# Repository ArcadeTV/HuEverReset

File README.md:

## HuEverReset
InGame-Reset for PC Engine with support for TurboEverdrive v1-v2.5

_*Important!*_ - Please consider waiting until everything is confirmed working.

### v20221109 / ArcadeTV

---

#### Description:
This enables an InGame-Reset by pressing a button-combo on the controller that also works with TurboEverdrive to get back to the menu.
It is designed for the white japanese PC Engine console but can be easily adapted to any PC Engine system if you know which pins of the controller-input-socket to connect to the pcb. Optionally you can use a piezo speaker for acoustic feedback upon triggering a reset.

---

#### Parts

| Part | Value               | Device           | Package             |
| :--- | :------------------ | :--------------- | :------------------ |
| CB1  | 100nF               | C-USC0805        | C0805               |
| C1   | 220uF               | CPOL-USC/6032-28R| C/6032-28R          |
| D1   | RB168VWM-40TR       | RB168VWM-40TR    | RB168VWM40TR        |
| IC1  | ATTINY84V-10SSUR    | ATTINY84V-10SSUR | SOIC127P600X175-14N |
| IC2  | KA78R05CTU_NL       | KA78R05          | TO-220-4            |
| R1   | 20K                 | R-US_R0805       | R0805               |
| R2   | 10K                 | R-US_R0805       | R0805               |
| R3   | 220                 | R-US_R0805       | R0805               |
| HDR  | 3-Pin Header 2.54mm | Pinheader        | Pinheader 2.54mm    |

Optionally, a piezo speaker like the [KPM-1205A](https://datasheetspdf.com/pdf/868392/Ningbo/KPM-1205A/1). A 220 Ohms resistor is recommended on the positive leg for attenuation. You can also wire a switch to the pads of J1 if you want to toggle this feature on and off.

Also optional a 5V Common Cathode LED can be used for visual feedback. It's lit constantly until the button combo is pressed, then it flashes to indicate that a reset will occur if the combo is pressed longer and finally it goes off while the reset is performed.

Here's a [BOM file in Excel format](https://github.com/ArcadeTV/HuEverReset/raw/main/BOM_HuEverReset_Mouser.xlsx) that you can use to order parts at Mouser. It does not include the KA78R05 regulator, LED and piezo speaker. Also please note that due to a general chip shortage you may have to source the ATtiny84 somewhere else.

---

#### Installation:
See the [wiki](https://github.com/ArcadeTV/HuEverReset/wiki)

---

#### Technical:
Since a TurboEverdrive v1 to v2.5 is not listening to a hard reset (/RESET), implementing an IngameReset that is triggered upon pressing a button-combo on the controller is not possible. This mod solves that problem by replacing the 7805 regulator with a KA78R05 that has a switchable output. So, instead of pulling the /RESET line of the PC Engine LOW, this mod aims to cut the power of the system for 1 second and turning it back on. This ensures that the menu of the TurboEverdrive is displayed. The pcb consists of 2 different layouts including a little POWER BOARD for making the replacement of the power-regulator a breeze.

---

#### Microcontroller:
```
ATtiny84 ----------------
                          _____
            VCC  (  ) 01-|°    |-14 (  ) GND
Jmp: Use Speaker (10) 02-|     |-13 (00) ENABLE (MiniDin 7)
     Speaker (+) (09) 03-|     |-12 (01) D3: Run, Left (MiniDin 5)
            N.C. (11) 04-|     |-11 (02) D2: Select, Down (MiniDin 4)
             LED (08) 05-|     |-10 (03) D1: II, Right (MiniDin 3)
            N.C. (07) 06-|     |-09 (04) SELECT (MiniDin 6)
          /RESET (06) 07-|_____|-08 (05) D0: I, Up (MiniDin 2)

| Fuses: 
| -----------
| low:   0xE2
| high:  0xD7
| ext.:  0xFF
| lock:  0xFF
```
Please mind that the ATtiny84 microcontroller needs to be programmed
with the provided hex file. If you use the ISP header on the pcb, please do so while the board is unpopulated except for IC1.

---

#### Jumper J1
Enable or Disable the use of a piezo speaker (buzzer).
```
Closed: use
Open: ignore
```
If you connect a piezo speaker for acoustic feedback when a reset is triggered, close J1. You may want to use a resistor on the positive leg of the speaker (e.g. 220 Ohms) if you find it too loud.

---

#### PCB

Use the provided gerber files to order your pcb from your favorite manufacturer. 
I recommend jlcpcb. When ordering from jlcpcb, fill out the order-form as follows:

```
Different Design: 2
Delivery Format: Panel by Customer
PCB Thickness: 0.8 - 1.0 mm
```

**GERBER** files can be downloaded from the `releases` tab: 

https://github.com/ArcadeTV/HuEverReset/releases/latest

Eagle source files for editing also exist in this repository.

---

#### Thanks

NeoRame, Astrocade & micro

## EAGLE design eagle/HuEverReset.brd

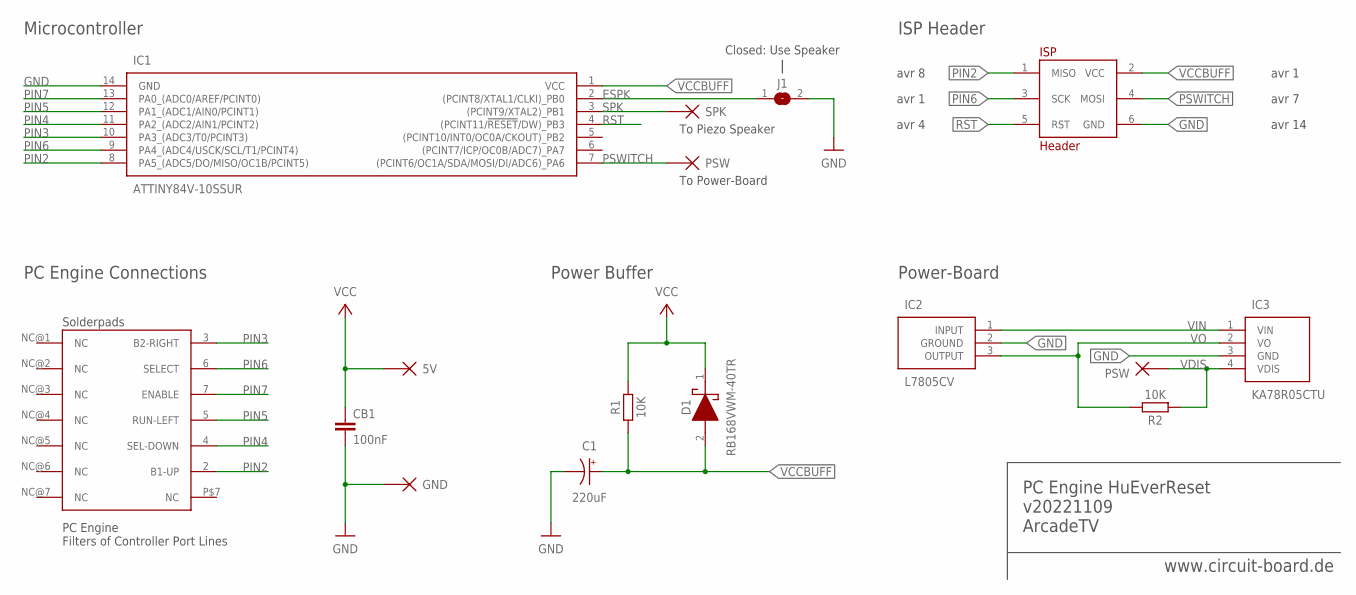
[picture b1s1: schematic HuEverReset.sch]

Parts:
C1: 220uF; C/6032-28R
CB1: 100nF; Z0805
D1: RB168VWM-40TR; RB168VWM40TR
IC1: ATTINY84V-10SSUR; SOIC127P600X175-14N
IC2: L7805CV; TO255P460X1020X2008-3P
IC3: KA78R05CTU; PADS
ISP: Header; TINY
J1: SJ
P1: 5V; PADS
P2: GND; PADS
P3: PSW; PADS
P4: SPK; PADS
R1, R2: 10K; Z0805
U$1: PCE-CNTRL-FILTERS
U$2: PSW; PADS

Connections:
ESPK: IC1.2 ((PCINT8/XTAL1/CLKI)_PB0), J1.1
GND: C1.-, CB1.2, IC1.14 (GND), IC2.2 (GROUND), IC3.3 (GND), ISP.6 (GND), J1.2, P2.P$1
PIN2: IC1.8 (PA5_(ADC5/DO/MISO/OC1B/PCINT5)), ISP.1 (MISO), U$1.2 (B1-UP)
PIN3: IC1.10 (PA3_(ADC3/T0/PCINT3)), U$1.3 (B2-RIGHT)
PIN4: IC1.11 (PA2_(ADC2/AIN1/PCINT2)), U$1.4 (SEL-DOWN)
PIN5: IC1.12 (PA1_(ADC1/AIN0/PCINT1)), U$1.5 (RUN-LEFT)
PIN6: IC1.9 (PA4_(ADC4/USCK/SCL/T1/PCINT4)), ISP.3 (SCK), U$1.6 (SELECT)
PIN7: IC1.13 (PA0_(ADC0/AREF/PCINT0)), U$1.7 (ENABLE)
PSWITCH: IC1.7 ((PCINT6/OC1A/SDA/MOSI/DI/ADC6)_PA6), ISP.4 (MOSI), P3.P$1
RST: IC1.4 ((PCINT11/!RESET!/DW)_PB3), ISP.5 (RST)
SPK: IC1.3 ((PCINT9/XTAL2)_PB1), P4.P$1
VCC: CB1.1, D1.1 (K), P1.P$1, R1.2
VCCBUFF: C1.+, D1.2 (A), IC1.1 (VCC), ISP.2 (VCC), R1.1
VDIS: IC3.4 (VDIS), R2.1, U$2.P$1
VIN: IC2.1 (INPUT), IC3.1 (VIN)
VO: IC2.3 (OUTPUT), IC3.2 (VO), R2.2

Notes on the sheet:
PC Engine HuEverReset v20221109 ArcadeTV
To Power-Board
Solderpads
PC Engine Filters of Controller Port Lines
Power-Board
To Piezo Speaker
ISP Header
avr 4
avr 1
avr 8
avr 7
avr 14
Power Buffer
PC Engine Connections
Microcontroller
www.circuit-board.de
Closed: Use Speaker

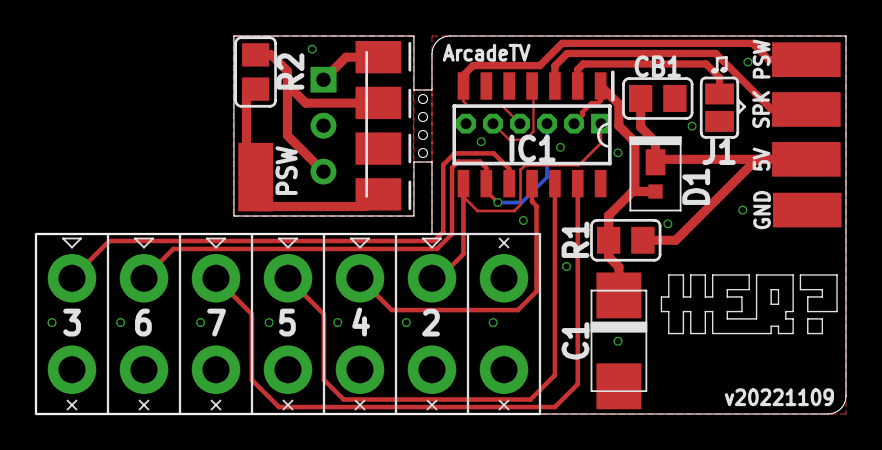
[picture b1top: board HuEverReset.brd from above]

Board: 2 copper layers, 45.0 x 21.0 mm, 16 parts (0 on the bottom side), 16 nets.

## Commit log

2022-11-07 Rename pceigr_v0.7.brd to eagle/HuEverReset_20221107.brd
2022-11-07 Rename pceigr_v0.7.sch to eagle/HuEverReset_20221107.sch
2022-11-08 Rename PCE-IGR.ino to ATtiny84/HuEverReset.ino
2022-11-09 Rename HuEverReset-pce_ATtiny84.hex to HuEverReset_ATtiny84.hex
2022-11-09 Rename HuEverReset_ATtiny84.ino to ATtiny84/HuEverReset_ATtiny84.ino
2022-11-12 Add Logo Vector Version
